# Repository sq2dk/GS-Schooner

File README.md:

# GS-Schooner
SP2ZIE Schooner Ground Station

This is repository for Ground Station for PWSat-3 satellite.

## Overview

Future PWSat-3 satellite will have communication module based on simplex operation on 437.xxxMHz. Modulation used would be most likely 2GFSK with downlink speeds from 1200bd up to maximum possible speeds which assure correct decoding. Uplink speeds will be probably limited to max 9600bd. Satellite will be using Endurosat UHF Transceiver II module, which seem to be based on one of the popular sub-gigahertz communications IC such as SI4463 or similar.

Simplex operation means that the same frequency will be used for uplink and transmit. This poses additional challenge of switching between transmitting and receiving, as the same antenna will be used both for transmit and receive side. Additionally to ensure effective communication with satellite, high transmit power should be used, and since satellite itself uses low power transmitter, ground station receiver has to be able to receive low signals. 

To help with weak signal receiving and maximizing power radiating by transmitter directional antennas have to be used. We have decided to use system of two shorter directional antennas rather, than one long antenna, as they are more manageable mechanicaly. Due to the undetermined orientation of satellite in space antennas have to have circular polarisation to avoid signal fade-outs.

Since antennas are directional, they need to be painted to satellite at all times – antenna rotator able to change position in azimuth and elevation is required.

To compensate for coaxial cable loss low noise amplifier for received signals is used placed next to the antenna. 

Due to high radio noise environment and presence of nearby high power transmitters on frequencies lying close to frequency of interest RF bandpass filter is added before LNA, not to saturate amplifier with unwanted signal.

Additional very low passband (about 100kHz) filter can be connected in line to further limit noise from unwanted transmissions. This filter due to low bandpass characteristic is tunable by stepper motor to tune to required frequency.

Received signal is further divided to 4 paths to allow simultaneous operation of up to 4 receivers (main station and up to 3 SDR receivers). Those might be essential to decode transmissions with speed of above 9600bd. 

TX path of the station leads directly from transmitter to antennas via 2 relays.

Yaesu FT-991 wash chosen as main transceiver. Although this radio is not specifically designed for satellite use, transceiver was only one currently in production and available on the market capable of producing 50W of RF power on 70cm band with 9600bd transmission/rx capability. 

## GS controller

Primary role of GS controller is managing switching between transmit and receive modes. Additionally block is additionally filtering and distributing signal for the receivers. All functions can be controlled by computer by serial protocol or manually by keys and encoders. On request from transmitter controller is checking if all conditions for transmit switching are meet and only then sends signal back to TRX to allow transmitting. Control and switching function as well as human interface functions are made by specially designed PCB based on STM blue pill microcontroller. Schematic of electronic circuit and PCB designed can be found in appropriate folder.  
Embedded software is written in Arduino environment and it is available in appropriate folder. 

## LNA Box

This part contains LNA, RF bandpass filter, RF relay and electronic driver for relay and LNA power supply. Schematic and PCB design for driver is included in appropriate folder. This is a simple transistor and relay switch. 4 wire interface to GS controlled is used. 12V power, ground, RX signal (to GND) and feedback signal are passed from/to GS controller. Separate TX and RX lines are feed from GS controller to LNA box. Although this solution requires extra coaxial cable, it simplifies design a bit, since other coaxial relay for TX/RX switching can be placed in below deck equipment (BDE).  
## Antenna system

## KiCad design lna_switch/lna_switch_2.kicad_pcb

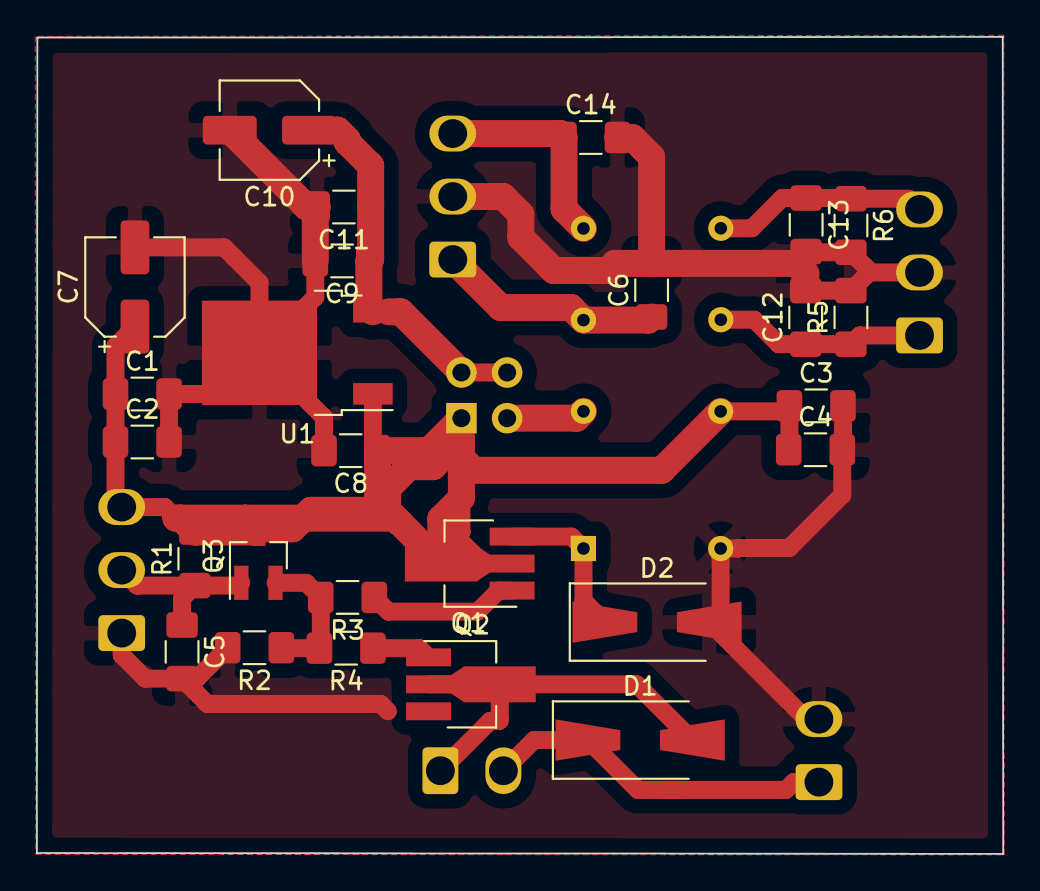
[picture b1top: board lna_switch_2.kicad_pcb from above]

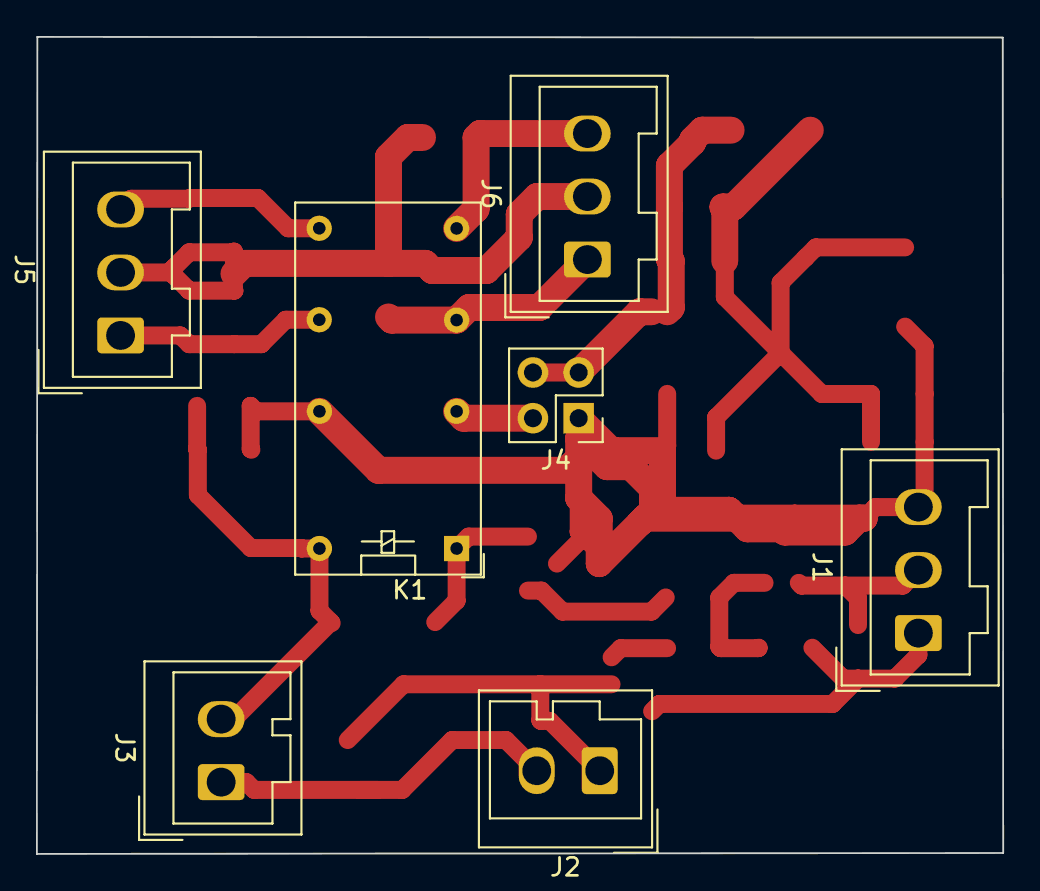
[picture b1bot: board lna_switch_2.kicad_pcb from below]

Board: 2 copper layers, 53.7 x 45.4 mm, 33 parts (7 on the bottom side), 15 nets.

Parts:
C1, C3, C11: 10n; C_1206_3216Metric_Pad1.42x1.75mm_HandSolder
C2, C4, C6, C8, C9, C12, C13, C14: 100n; C_1206_3216Metric_Pad1.42x1.75mm_HandSolder
C5: 1n; C_1206_3216Metric_Pad1.42x1.75mm_HandSolder
C7: CP; CP_Elec_5x3
C10: 10u; CP_Elec_5x3
D1, D2: M7; D_SMA-SMB_Universal_Handsoldering
J1: Conn_01x03; Wago_734-133_1x03_P3.50mm_Vertical
J2: Conn_Relay; Wago_734-132_1x02_P3.50mm_Vertical
J3: 26V; Wago_734-132_1x02_P3.50mm_Vertical
J4: Conn_02x02_Counter_Clockwise; PinHeader_2x02_P2.54mm_Vertical
J5: Feedback; Wago_734-133_1x03_P3.50mm_Vertical
J6: LNA_conn; Wago_734-133_1x03_P3.50mm_Vertical
K1: G5V-2; Relay_DPDT_Omron_G5V-2
Q1, Q2: BCX54; SOT-89-3_Handsoldering
Q3: BC848; SOT-23_Handsoldering
R1: 1.2k; R_1206_3216Metric_Pad1.42x1.75mm_HandSolder
R2: 4.7k; R_1206_3216Metric_Pad1.42x1.75mm_HandSolder
R3, R4: 470; R_1206_3216Metric_Pad1.42x1.75mm_HandSolder
R5, R6: 1,2k; R_1206_3216Metric_Pad1.42x1.75mm_HandSolder
U1: KA78M05_TO252; TO-252-2

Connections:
+12V: C1.1, C2.1, C3.1, C4.1, C7.1, C8.1, J1.3, J4.1, K1.13, Q1.2, Q3.3, R1.2, U1.1
GND: C1.2, C2.2, C3.2, C4.2, C5.2, C6.2, C7.2, C8.2, C9.2, C10.2, C11.2, C12.2, C13.2, C14.2, D2.2, J1.1, J3.2, J5.2, J6.2, K1.16, R2.2, R5.2, R6.2, U1.2
unnamed: C5.1, J1.2, Q3.1, R1.1
unnamed: C6.1, J6.1, K1.6
unnamed: C9.1, C10.1, C11.1, J4.3, J4.4, U1.3
unnamed: C12.1, J5.1, K1.11, R5.1
unnamed: C13.1, J5.3, K1.9, R6.1
unnamed: C14.1, J6.3, K1.8
unnamed: D1.1, J2.2, J3.1
unnamed: D1.2, J2.1, Q2.2
unnamed: D2.1, K1.1, Q1.3
unnamed: J4.2, K1.4
unnamed: Q1.1, R3.1
unnamed: Q2.1, R4.1
unnamed: Q3.2, R2.1, R3.2, R4.2

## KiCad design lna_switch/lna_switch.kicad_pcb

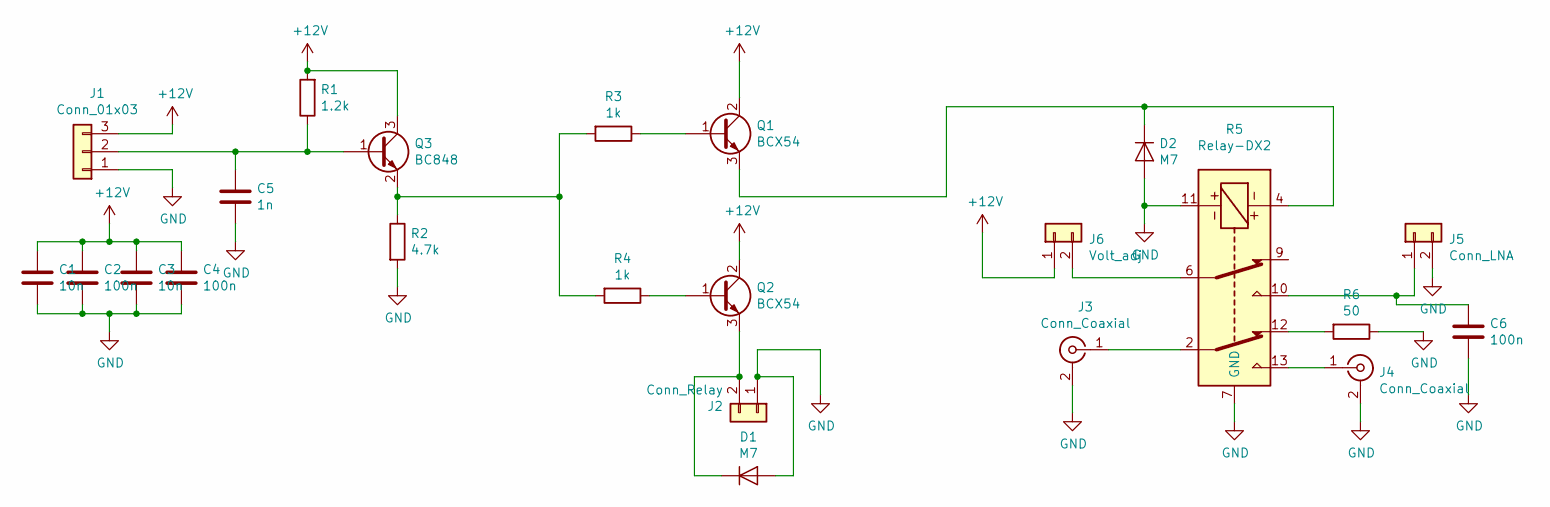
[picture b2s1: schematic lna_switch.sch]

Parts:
C1, C3: 10n; C_1206_3216Metric_Pad1.42x1.75mm_HandSolder
C2, C4, C6: 100n; C_1206_3216Metric_Pad1.42x1.75mm_HandSolder
C5: 1n; C_1206_3216Metric_Pad1.42x1.75mm_HandSolder
D1, D2: M7; D_SMA-SMB_Universal_Handsoldering
J1: Conn_01x03; PinHeader_1x03_P2.54mm_Vertical
J2: Conn_Relay; PinHeader_1x02_P2.54mm_Vertical
J3, J4: Conn_Coaxial; SMA_Samtec_SMA-J-P-H-ST-EM1_EdgeMount
J5: Conn_LNA; PinHeader_1x02_P2.54mm_Vertical
J6: Volt_adj; PinHeader_1x02_P2.54mm_Vertical
Q1, Q2: BCX54; SOT-89-3_Handsoldering
Q3: BC848; SOT-23_Handsoldering
R1: 1.2k; R_1206_3216Metric_Pad1.42x1.75mm_HandSolder
R2: 4.7k; R_1206_3216Metric_Pad1.42x1.75mm_HandSolder
R3, R4: 1k; R_1206_3216Metric_Pad1.42x1.75mm_HandSolder
R5: Relay-DX2; DIP-14_W7.62mm_LongPads
R6: 50; R_1206_3216Metric_Pad1.42x1.75mm_HandSolder

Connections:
+12V: C1.1, C2.1, C3.1, C4.1, J1.3, J6.1, Q1.2 (C), Q2.2 (C), Q3.3 (C), R1.2
GND: C1.2, C2.2, C3.2, C4.2, C5.2, C6.2, D1.2 (A), D2.2 (A), J1.1, J2.1, J3.2 (Ext), J4.2 (Ext), J5.2, R2.2, R5.7 (GND), R5.11, R6.1
unnamed: C5.1, J1.2, Q3.1 (B), R1.1
unnamed: C6.1, J5.1, R5.10
unnamed: D1.1 (K), J2.2, Q2.3 (E)
unnamed: D2.1 (K), Q1.3 (E), R5.4
unnamed: J3.1 (In), R5.2
unnamed: J4.1 (In), R5.13
unnamed: J6.2, R5.6
unnamed: Q1.1 (B), R3.1
unnamed: Q2.1 (B), R4.1
unnamed: Q3.2 (E), R2.1, R3.2, R4.2
unnamed: R5.1, R5.3, R5.5, R5.8, R5.14
unnamed: R5.12, R6.2

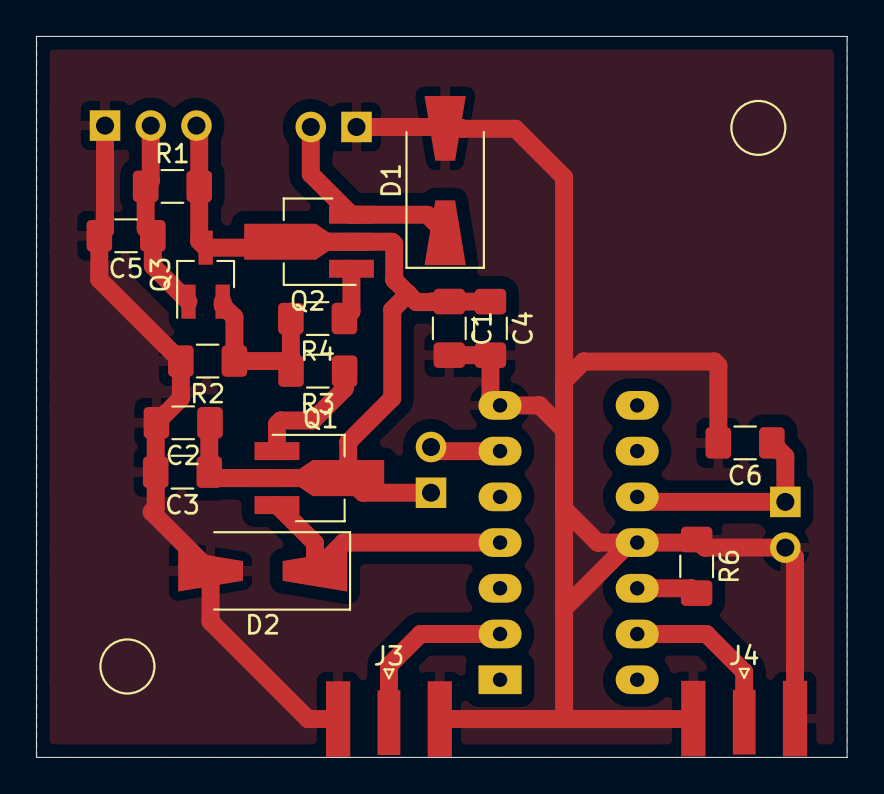
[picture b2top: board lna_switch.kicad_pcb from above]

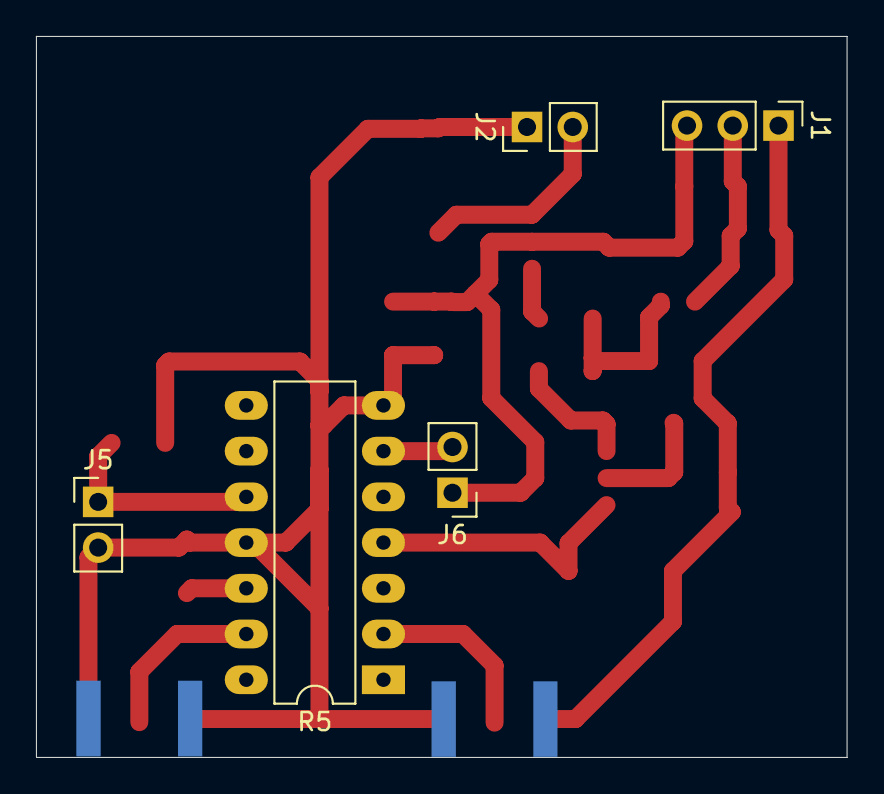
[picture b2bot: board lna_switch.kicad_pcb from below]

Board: 2 copper layers, 45.0 x 40.1 mm, 23 parts (5 on the bottom side), 14 nets.

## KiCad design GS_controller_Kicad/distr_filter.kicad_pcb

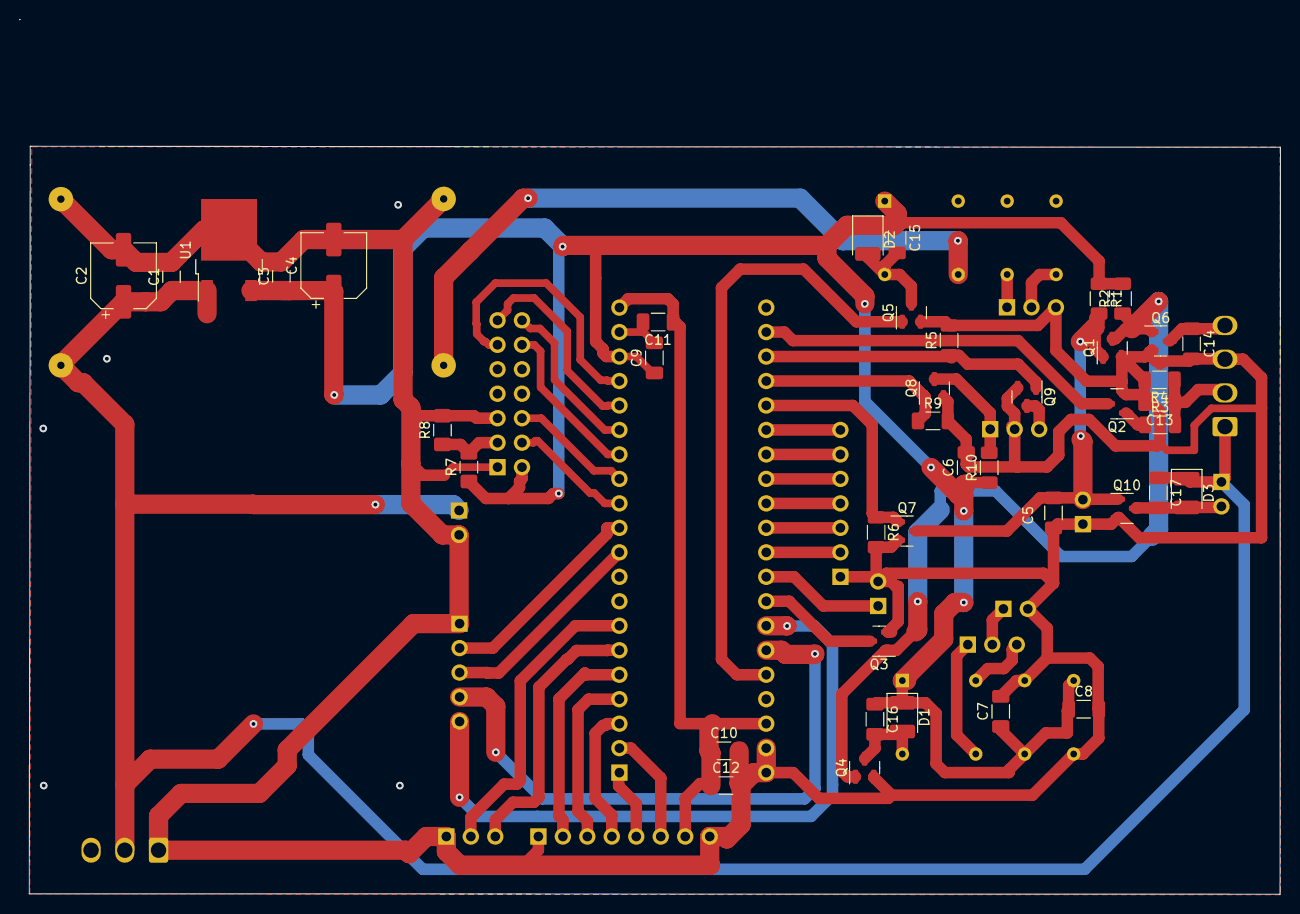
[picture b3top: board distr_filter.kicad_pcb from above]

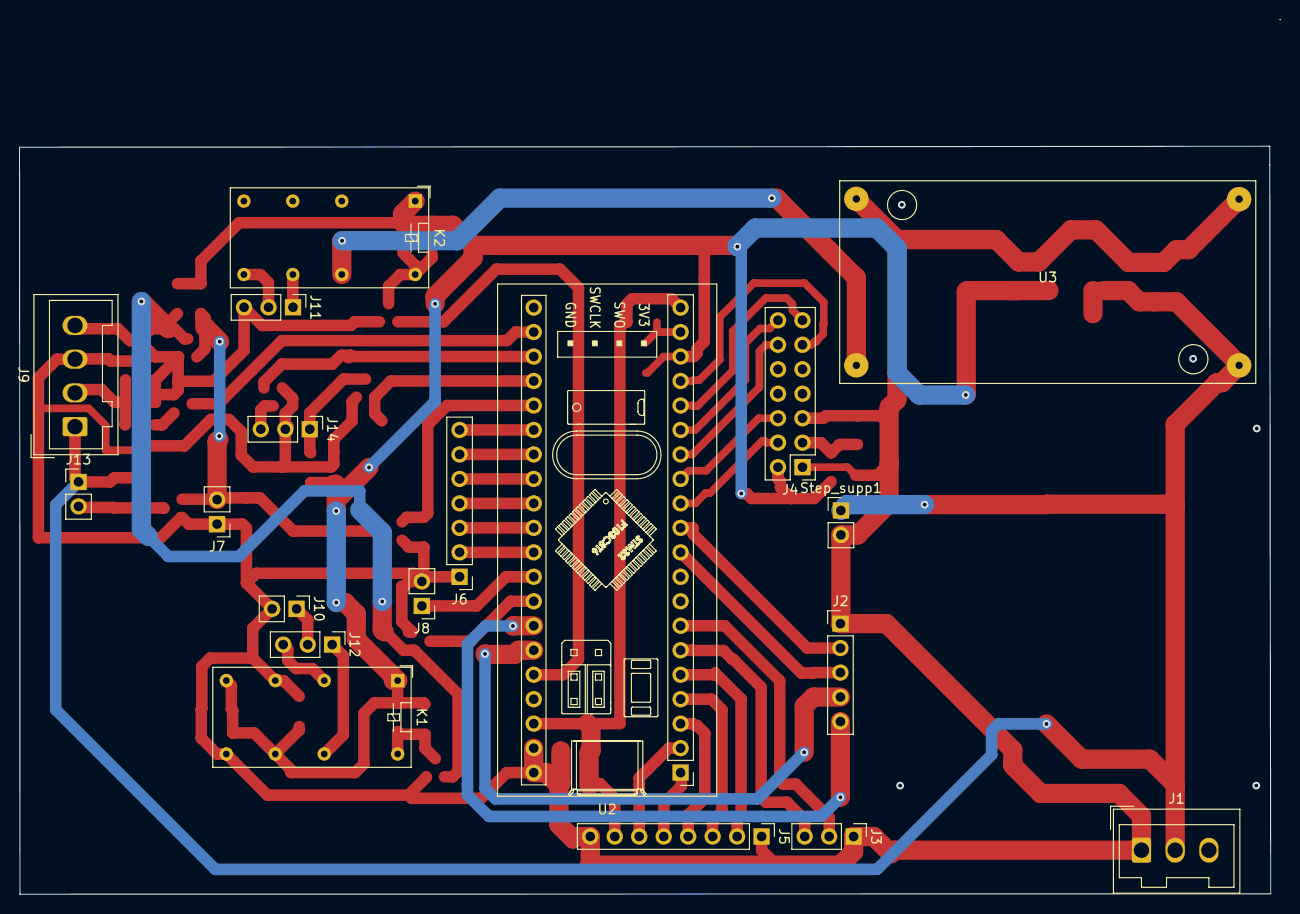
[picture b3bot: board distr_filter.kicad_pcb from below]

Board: 2 copper layers, 130.9 x 90.8 mm, 60 parts (19 on the bottom side), 51 nets.

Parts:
C1, C3: 100n; C_1206_3216Metric_Pad1.42x1.75mm_HandSolder
C2, C4: 10u; CP_Elec_6.3x5.7
C5: 1n; C_1206_3216Metric_Pad1.33x1.80mm_HandSolder
C6, C7, C8, C9, C10, C11, C12, C13: 10n; C_1206_3216Metric_Pad1.33x1.80mm_HandSolder
C14, C15, C16, C17: 100n; C_1206_3216Metric_Pad1.33x1.80mm_HandSolder
D1, D2, D3: D; D_1210_3225Metric_Pad1.42x2.65mm_HandSolder
J1: 13.8V In; Wago_734-133_1x03_P3.50mm_Vertical
J2: Stepper; PinHeader_1x05_P2.54mm_Vertical
J3: RS232; PinHeader_1x03_P2.54mm_Vertical
J4: LCD_DISP; PinHeader_2x07_P2.54mm_Vertical
J5: KEY_CON; PinHeader_1x08_P2.54mm_Vertical
J6: ATT_CON; PinHeader_1x07_P2.54mm_Vertical
J7: PTT_In; PinHeader_1x02_P2.54mm_Vertical
J8: Fltr_lim; PinHeader_1x02_P2.54mm_Vertical
J9: LNA_BOX; Wago_734-134_1x04_P3.50mm_Vertical
J10: LNA_V; PinHeader_1x02_P2.54mm_Vertical
J11: Bypass; PinHeader_1x03_P2.54mm_Vertical
J12: NOR_ON; PinHeader_1x03_P2.54mm_Vertical
J13: Relay_dist; PinHeader_1x02_P2.54mm_Vertical
J14: PTT_IO; PinHeader_1x03_P2.54mm_Vertical
K1, K2: G5V-2; Relay_DPDT_Omron_G5V-2
Q1, Q8: BC848; SOT-23
Q2, Q3, Q4, Q5, Q6, Q7, Q9, Q10: 2N7002; SOT-23
R1, R3, R4, R5, R6, R9, R10: 4k7; R_1206_3216Metric_Pad1.30x1.75mm_HandSolder
R2: 10k; R_1206_3216Metric_Pad1.30x1.75mm_HandSolder
R7, R8: R; R_1206_3216Metric_Pad1.42x1.75mm_HandSolder
Step_supp1: Conn_01x02; PinHeader_1x02_P2.54mm_Vertical
U1: L7805; TO-252-2
U2: YAAJ_BluePill_Part_Like; YAAJ_BluePill_1
U3: XL6009E1; XL6009E

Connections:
+3V3: C10.1, C11.1, C12.1, J5.7, U2.20 (3V3), U2.38 (3V3)
+5V: C3.1, C4.1, C6.1, C7.1, C8.1, C9.1, C15.1, C16.1, D1.1 (K), D2.1 (K), J4.2, K1.1, K1.8, K1.11, K2.1, R1.1, R2.2, R7.1, R10.1, U1.3 (OUT), U2.18 (5V)
+12V: C1.1, C2.1, C17.1, D3.1 (K), J1.2, J9.1, J13.1, Step_supp1.1, U1.1 (IN), U3.1 (In+)
GND: C1.2, C2.2, C3.2, C4.2, C5.2, C6.2, C7.2, C8.2, C9.2, C10.2, C11.2, C12.2, C13.2, C14.2, J1.1, J2.1, J3.1, J4.1, J4.5, J5.1, J5.8, J6.1, J7.1, J8.2, J9.3, J10.2, J11.3, J14.2, K1.6, K1.9, Q1.2 (E), Q2.2 (S), Q3.2 (S), Q4.2 (S), Q5.2 (S), Q6.2 (S), Q7.2 (S), Q8.2 (E), Q9.2 (S), Q10.2 (S), R4.2, R5.2, R6.2, R8.2, R9.2, Step_supp1.2, U1.2 (GND), U2.19 (GND), U2.39 (GND), U2.40 (GND), U3.2 (In-), U3.4 (Out-)
unnamed: C5.1, J7.2, Q1.1 (B), Q7.3 (D), Q10.1 (G), R1.2
unnamed: C13.1, J9.2, R3.2, R4.1
unnamed: C14.1, J9.4, Q6.3 (D)
unnamed: C15.2, D2.2 (A), K2.16, Q5.3 (D)
unnamed: C16.2, D1.2 (A), K1.16, Q4.3 (D)
unnamed: C17.2, D3.2 (A), J13.2, Q10.3 (D)
unnamed: J2.2, U2.11 (PB3)
unnamed: J2.3, U2.10 (PA15)
unnamed: J2.4, U2.35 (PB10)
unnamed: J2.5, U2.34 (PB1)
unnamed: J3.2, U2.7 (PA10)
unnamed: J3.3, U2.6 (PA9)
unnamed: J4.3, R7.2, R8.1
unnamed: J4.4, U2.12 (PB4)
unnamed: J4.6, U2.13 (PB5)
unnamed: J4.11, U2.17 (PB9)
unnamed: J4.12, U2.14 (PB6)
unnamed: J4.13, U2.16 (PB8)
unnamed: J4.14, U2.15 (PB7)
unnamed: J5.2, U2.5 (PA8)
unnamed: J5.3, U2.4 (PB15)
unnamed: J5.4, U2.3 (PB14)
unnamed: J5.5, U2.1 (PB12)
unnamed: J5.6, U2.2 (PB13)
unnamed: J6.2, U2.31 (PA6)
unnamed: J6.3, U2.30 (PA5)
unnamed: J6.4, U2.29 (PA4)
unnamed: J6.5, U2.28 (PA3)
unnamed: J6.6, U2.27 (PA2)
unnamed: J6.7, U2.26 (PA1)
unnamed: J8.1, U2.32 (PA7)
unnamed: J10.1, J12.2
unnamed: J11.1, K2.11
unnamed: J11.2, K2.9
unnamed: J12.1, K1.13
unnamed: J12.3, K1.4
unnamed: J14.1, Q8.3 (C), R10.2
unnamed: K2.13, U3.3 (Out+)
unnamed: Q1.3 (C), Q3.1 (G), Q4.1 (G), Q6.1 (G), R2.1
unnamed: Q2.1 (G), R3.1
unnamed: Q2.3 (D), U2.22 (PC13)
unnamed: Q3.3 (D), U2.33 (PB0)
unnamed: Q5.1 (G), U2.36 (PB11)
unnamed: Q7.1 (G), R6.1, U2.25 (PA0)
unnamed: Q8.1 (B), R9.1, U2.24 (PC15)
unnamed: J14.3, Q9.3 (D)
unnamed: Q9.1 (G), R5.1, U2.23 (PC14)

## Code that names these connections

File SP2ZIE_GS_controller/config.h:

#ifndef CONFIG_H
#define CONFIG_H

//Serial 1 ports are:
// PB9 - TX
// PB10 - RX

// Stepper motor pins
#define motor_pin_D PB10
#define motor_pin_C PB1
#define motor_pin_B PA15
#define motor_pin_A PB3

#define filter_limit_pin PA7

#define CABLE_CONNECTED PB4

#define LED_Y PB5
#define LED_R PB8

#define KEY_L PB13
#define KEY_R PB12

#define ENC_PRESS PA8
#define ENC_CLK PB15
#define ENC_DATA PB14



#define VOLT_INP PA1

// Attenuator pins
#define ATT_V1 PB9    //LSB
#define ATT_V2 PA2
#define ATT_V3 PA3
#define ATT_V4 PA4
#define ATT_V5 PA5
#define ATT_V6 PA6    //MSB

//filter bypass pin
#define FLTR_BPS PB11

//transmit pin (should switch off power to LNA and force max attenaution
#define PTT_IN PB0

#define LNA_BOX_SW PC13       // TX/RX switch feedback from LNA box
#define PTT_FORCE PA0         // Force TX by microcontroler
#define PTT_OUT PC14          // PTT OUT to radio - controlled by microcontroller
#define PTT_INH PC15          // When high (high resistance) no TX is possible (yaesu)
#define LNABOX_FEEDBACK PC13  // Feedback from LNA BOX

#define KEY1 PB12
#define KEY2 PB13
#define KEY3 PB14
#define ENC_PIN1 PB15
#define ENC_PIN2 PB8



#endif // CONFIG_H

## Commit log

2023-12-20 First release - very much work in progress...
    First semi-functional release of SP2ZIE GS controller.
    Bluepill arduino code
2023-12-20 Kicad schematic of GS controller board
    Quick and dirt - PCB not updated with latest changes. Design changes reuired - LCD based on i2c now, some pins (former LCD) used for other functions (cable conn det, etc). PA1 pin reassigned for anal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
2023-12-20 Pictures of controller
2023-12-27 Add files via upload
    Minor changes:
    -added watchdog - controller has some tendency for "hanging" while manual tuning
    -added debug level (by default minimum communication on serial)
    -added new serial command "ST?" which returns "STST" status line
2023-12-27 TX / RX switch controller for LNA box
    Initial commit
2023-12-28 Updated -Bypass- disp ix
    update made in Club
    -bypass disp ix
    -bypass eng at beging
2024-01-03 Updated and proed changes. Mostly about bypass action
    Checked on working device.
2024-01-04 Controller picture in a system
2024-07-04 Block schematic of SP2ZIE Schooner ground station
2024-07-04 GS antenna system
2024-07-04 LNA box block schematic
2024-07-04 LNA box picture
2024-07-05 Block schematic of ground station
2024-07-05 Block diagram of ground station
